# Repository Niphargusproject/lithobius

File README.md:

# lithobius
Lithobius environmental logger

Update 19/06/2023:
First upload of PCB & firmware for the Moteino version.
TODO: BOM & Manual

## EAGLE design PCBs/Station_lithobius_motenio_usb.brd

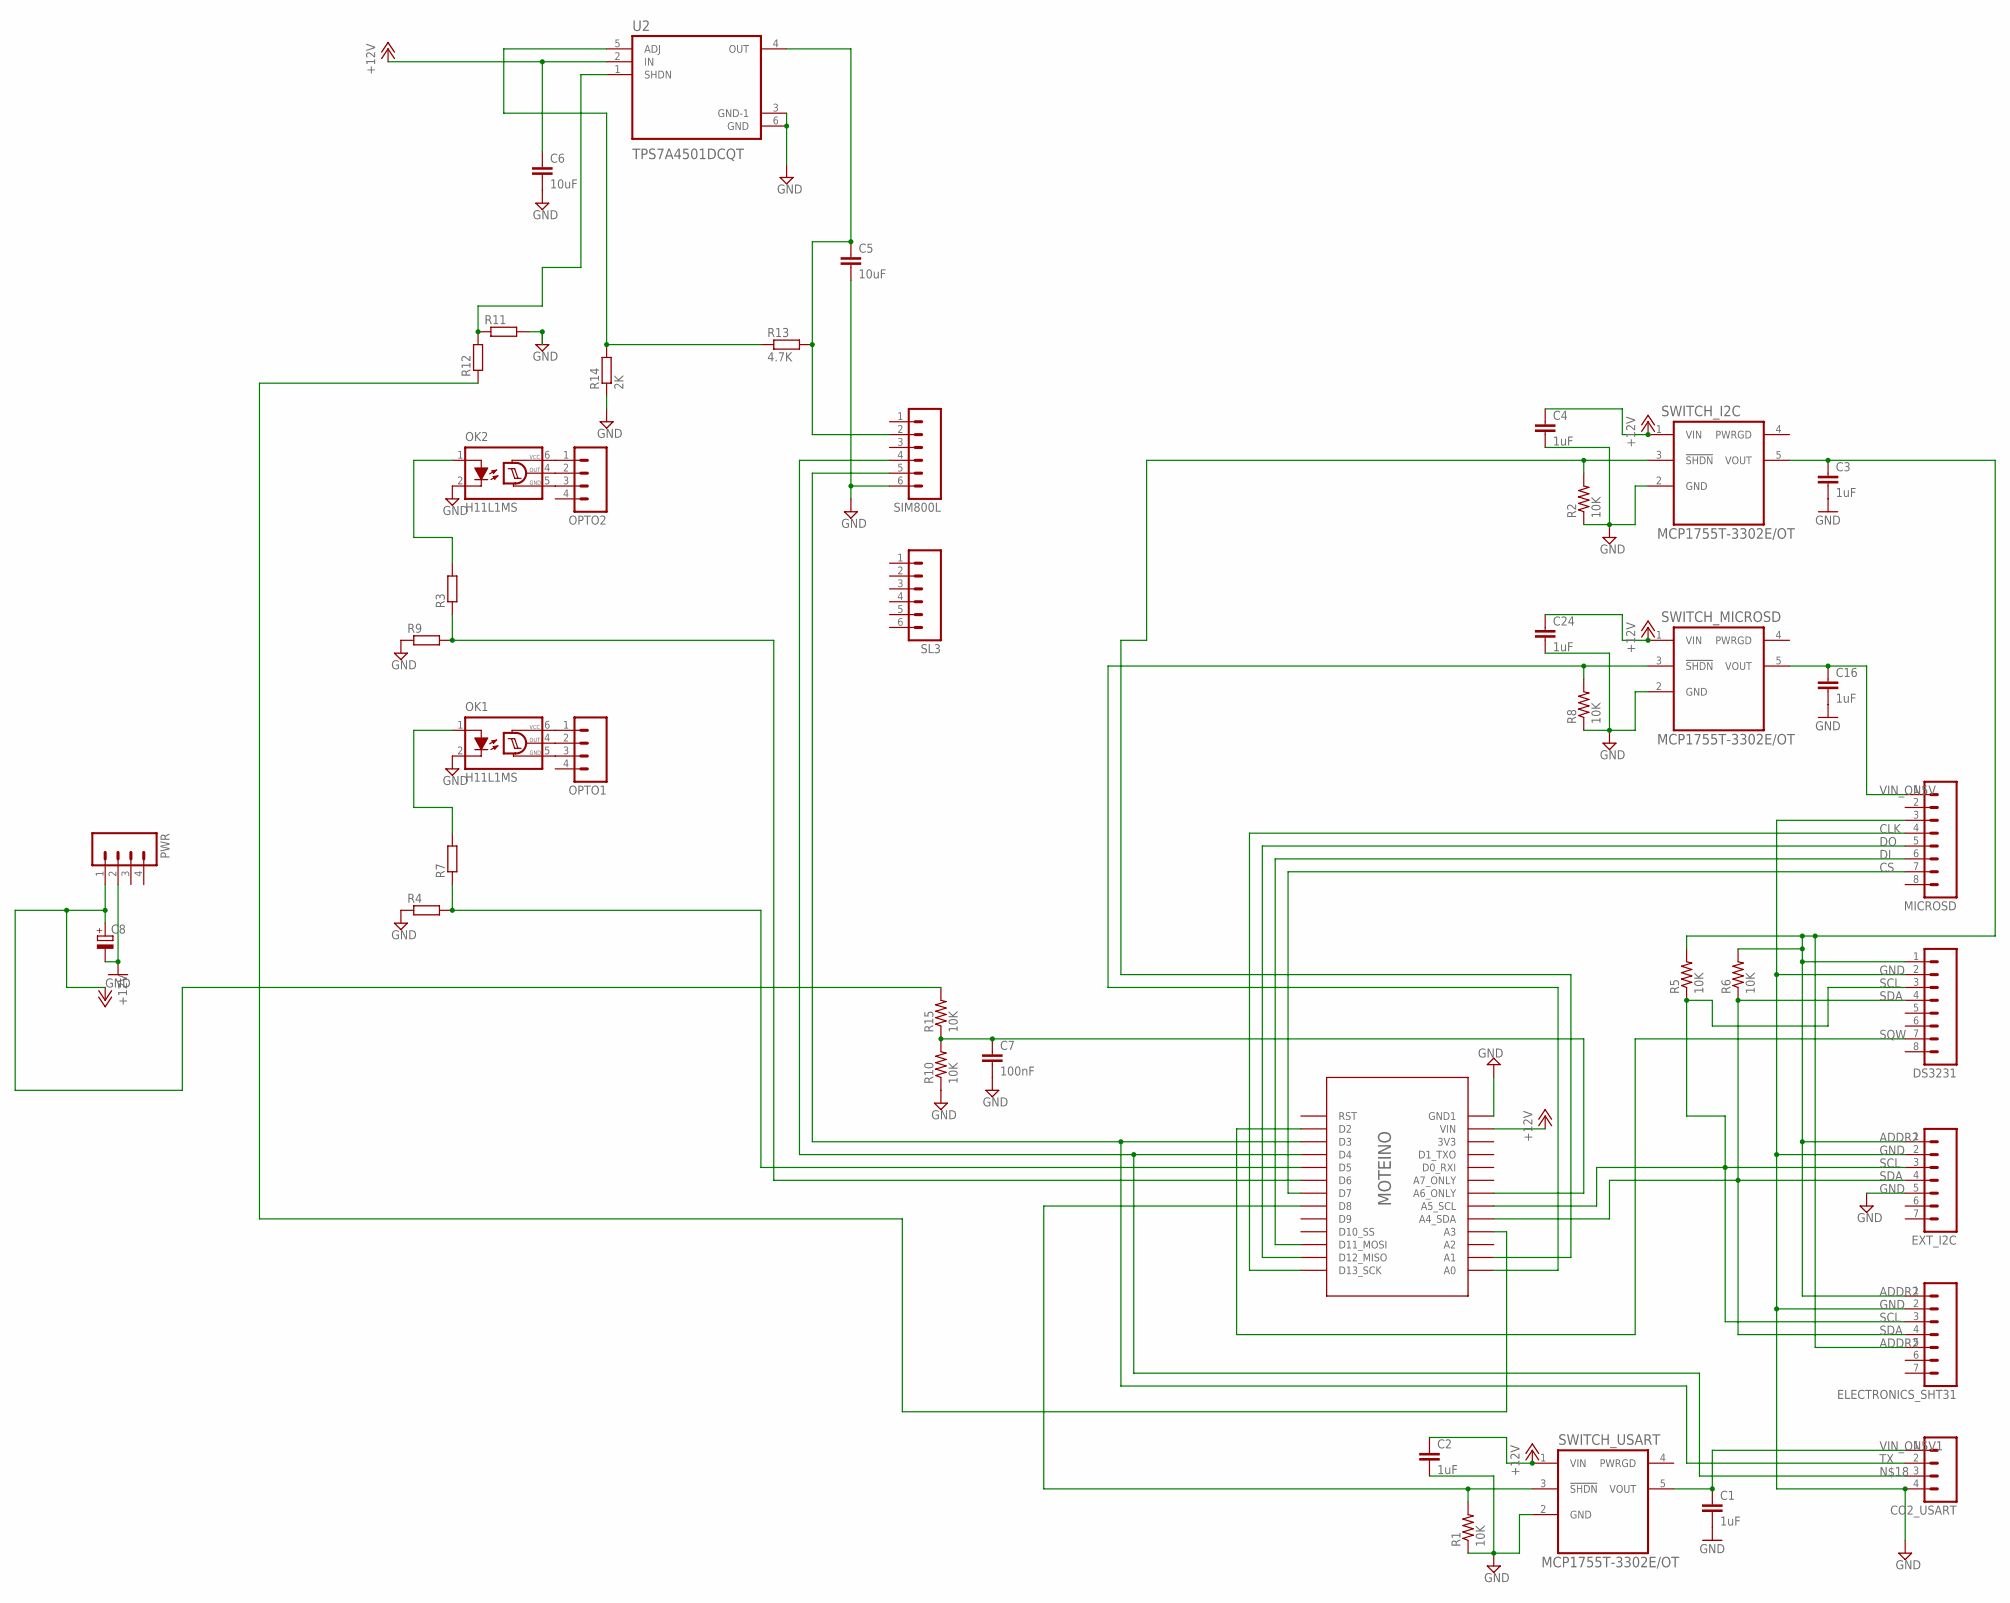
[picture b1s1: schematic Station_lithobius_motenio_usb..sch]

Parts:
C1, C2, C3, C4, C16, C24: 1uF; C0805K
C5, C6: 10uF; C0805K
C7: 100nF; C0805K
C8: CPOL-EU153CLV-0810; 153CLV-0810
CO2_USART: M04; 04P
DS3231: M08; 08P
ELECTRONICS_SHT31: M07; 07P
EXT_I2C: M07; 07P
MICROSD: M08; 08P
OK1, OK2: H11L1MS; DIL6-SMD
OPTO1, OPTO2: M04; 04P
PWR: M04; 04P
R1, R2, R5, R6, R8, R10, R15: 10K; R2012W
R3, R4, R7, R9, R11, R12: R-EU_R0805; R0805
R13: 4.7K; R0805
R14: 2K; R0805
SIM800L: M06; 06P
SL3: M06; 06P
SWITCH_I2C: MCP1755T-3302E/OT; SOT95P270X145-5N
SWITCH_MICROSD: MCP1755T-3302E/OT; SOT95P270X145-5N
SWITCH_USART: MCP1755T-3302E/OT; SOT95P270X145-5N
U2: TPS7A4501DCQT; SOT127P706X180-6N
U$1: MOTEINO_SIMPLE

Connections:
+12V: C2.1, C4.1, C6.1, C8.+, C24.1, PWR.1, R15.2, SWITCH_I2C.1 (VIN), SWITCH_MICROSD.1 (VIN), SWITCH_USART.1 (VIN), U2.2 (IN), U$1.VIN
ADDR2: C3.1, DS3231.1, ELECTRONICS_SHT31.1, ELECTRONICS_SHT31.5, EXT_I2C.1, R5.2, R6.2, SWITCH_I2C.5 (VOUT)
CLK: MICROSD.4, U$1.D13_SCK
CS: MICROSD.7, U$1.D7
DI: MICROSD.6, U$1.D11_MOSI
DO: MICROSD.5, U$1.D12_MISO
GND: C1.2, C2.2, C3.2, C4.2, C5.2, C6.2, C7.2, C8.-, C16.2, C24.2, CO2_USART.4, DS3231.2, ELECTRONICS_SHT31.2, EXT_I2C.2, EXT_I2C.5, MICROSD.3, OK1.2 (C), OK2.2 (C), PWR.2, R1.1, R2.1, R4.1, R8.1, R9.1, R10.1, R11.2, R14.1, SIM800L.6, SWITCH_I2C.2 (GND), SWITCH_MICROSD.2 (GND), SWITCH_USART.2 (GND), U2.3 (GND-1), U2.6 (GND), U$1.GND1
unnamed: R11.1, R12.2, U2.1 (SHDN)
unnamed: R2.2, SWITCH_I2C.3 (!SHDN), U$1.A1
unnamed: R4.2, R7.1, U$1.D5
unnamed: OK1.6 (VCC), OPTO1.1
unnamed: C7.1, R10.2, R15.1, U$1.A6_ONLY
unnamed: R1.2, SWITCH_USART.3 (!SHDN), U$1.D8
unnamed: R3.1, R9.2, U$1.D6
unnamed: OK1.4 (OUT), OPTO1.2
unnamed: OK1.5 (GND), OPTO1.3
unnamed: OK1.1 (A), R7.2
unnamed: R12.1, U$1.A3
unnamed: OK2.6 (VCC), OPTO2.1
unnamed: OK2.4 (OUT), OPTO2.2
unnamed: C5.1, R13.2, SIM800L.2, U2.4 (OUT)
unnamed: R13.1, R14.2, U2.5 (ADJ)
unnamed: CO2_USART.3, SIM800L.4, U$1.D4
unnamed: OK2.5 (GND), OPTO2.3
unnamed: OK2.1 (A), R3.2
unnamed: R8.2, SWITCH_MICROSD.3 (!SHDN), U$1.A0
SCL: DS3231.3, ELECTRONICS_SHT31.3, EXT_I2C.3, R5.1, U$1.A5_SCL
SDA: DS3231.4, ELECTRONICS_SHT31.4, EXT_I2C.4, R6.1, U$1.A4_SDA
SQW: DS3231.7, U$1.D2
TX: CO2_USART.2, SIM800L.5, U$1.D3
VIN_ON5V: C16.1, MICROSD.1, SWITCH_MICROSD.5 (VOUT)
VIN_ON5V1: C1.1, CO2_USART.1, SWITCH_USART.5 (VOUT)

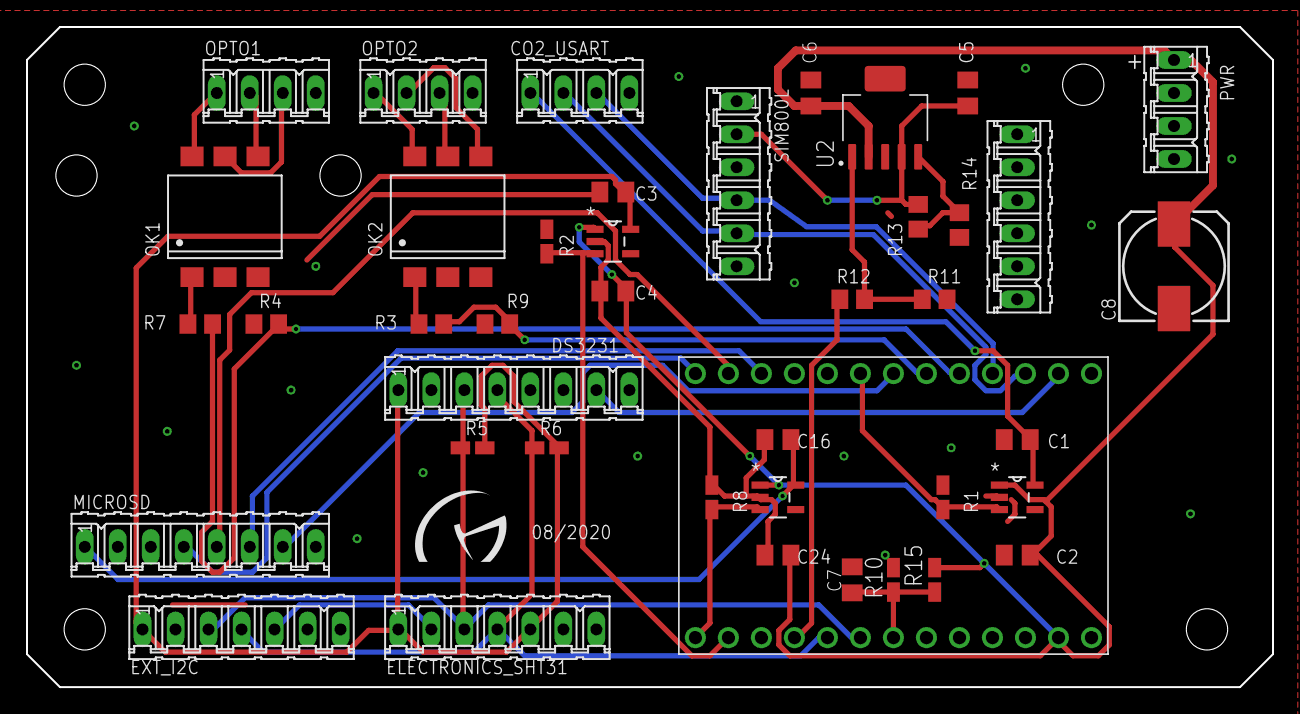
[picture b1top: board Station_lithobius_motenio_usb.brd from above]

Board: 2 copper layers, 95.9 x 50.8 mm, 42 parts (0 on the bottom side), 32 nets.

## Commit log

2023-06-19 first commit (basic temperature example)
2023-08-23 Auto stash before rebase of "refs/heads/main"
